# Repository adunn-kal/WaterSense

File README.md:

# WaterSense
 Main firmware for the Water Sense project.
 
 See https://adunn-kal.github.io/WaterSense/ for more details.

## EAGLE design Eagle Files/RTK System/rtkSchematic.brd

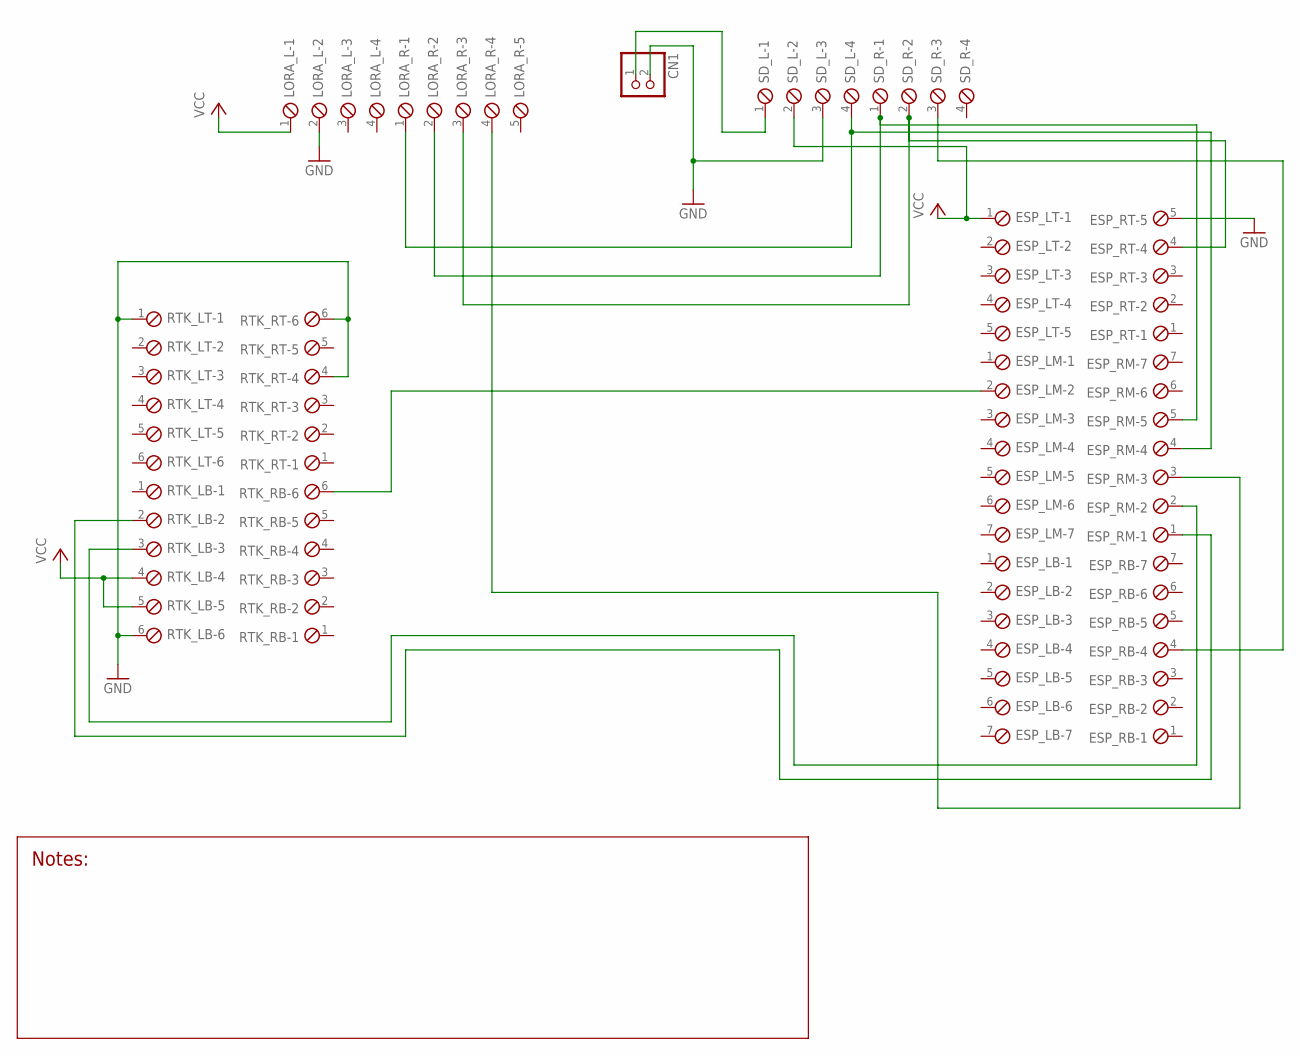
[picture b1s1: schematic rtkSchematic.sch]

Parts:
CN1: JST_2PIN-SMT-RA; JST-PH-2-SMT-RA
ESP_LB: SCREWTERM_7P_254; 7POL254
ESP_LM: SCREWTERM_7P_254; 7POL254
ESP_LT: SCREWTERM_5P_254; 5POL254
ESP_RB: SCREWTERM_7P_254; 7POL254
ESP_RM: SCREWTERM_7P_254; 7POL254
ESP_RT: SCREWTERM_5P_254; 5POL254
LORA_L: SCREWTERM_4P_254; 4POL254
LORA_R: SCREWTERM_5P_254; 5POL254
RTK_LB: SCREWTERM_6P_254; 6POL254
RTK_LT: SCREWTERM_6P_254; 6POL254
RTK_RB: SCREWTERM_6P_254; 6POL254
RTK_RT: SCREWTERM_6P_254; 6POL254
SD_L: SCREWTERM_4P_254; 4POL254
SD_R: SCREWTERM_4P_254; 4POL254

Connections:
GND: CN1.2 (1), ESP_RT.5, LORA_L.2, RTK_LB.6, RTK_LT.1, RTK_RT.4, RTK_RT.6, SD_L.3
unnamed: ESP_LM.2, RTK_RB.6
unnamed: CN1.1 (2), SD_L.1
unnamed: ESP_RM.4, LORA_R.1, SD_L.4
unnamed: ESP_RM.5, LORA_R.2, SD_R.1
unnamed: ESP_RT.4, LORA_R.3, SD_R.2
unnamed: ESP_RB.4, SD_R.3
unnamed: ESP_RM.2, RTK_LB.3
unnamed: ESP_RM.1, RTK_LB.2
unnamed: ESP_RM.3, LORA_R.4
VCC: ESP_LT.1, LORA_L.1, RTK_LB.4, RTK_LB.5, SD_L.2

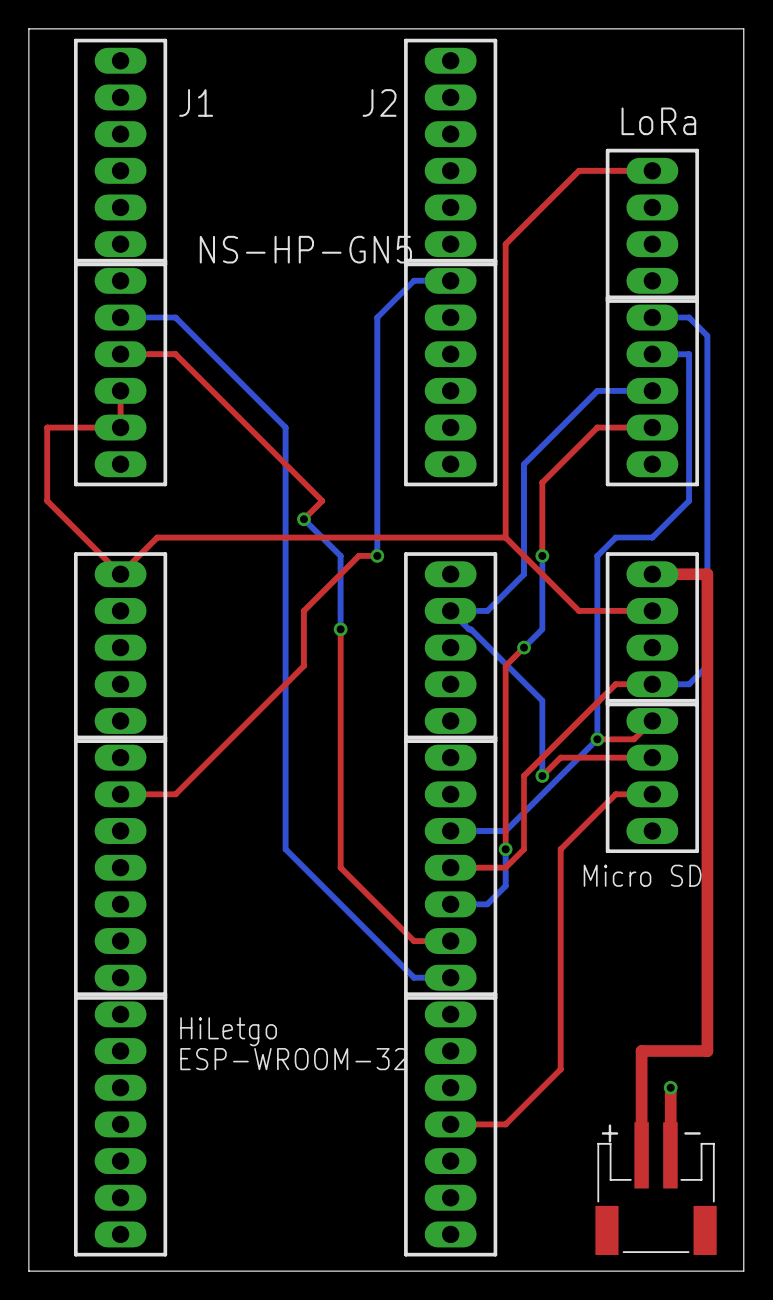
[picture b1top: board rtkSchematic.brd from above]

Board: 2 copper layers, 49.5 x 86.0 mm, 15 parts (0 on the bottom side), 11 nets.

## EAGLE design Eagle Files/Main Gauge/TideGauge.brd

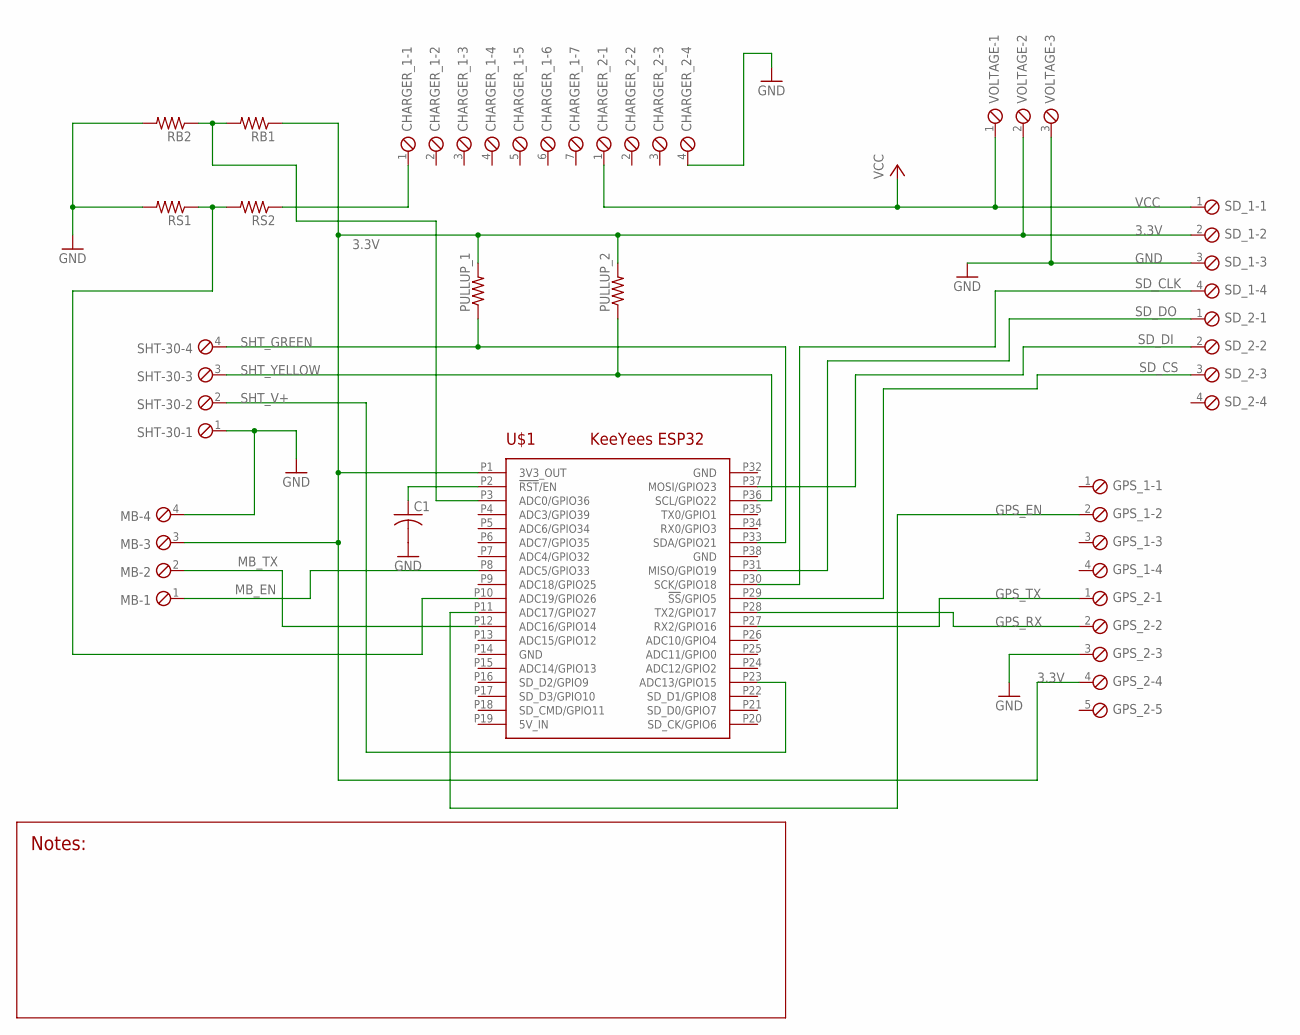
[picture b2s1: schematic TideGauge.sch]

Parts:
C1: C-USC0805; C0805
CHARGER_1: SCREWTERM_7P_254; 7POL254
CHARGER_2: SCREWTERM_4P_254; 4POL254
GPS_1: SCREWTERM_4P_254; 4POL254
GPS_2: SCREWTERM_5P_254; 5POL254
MB: SCREWTERM_4P_254; 4POL254
PULLUP_1, PULLUP_2: R-US_M0805; M0805
RB1, RB2: R-US_R0805; R0805
RS1, RS2: R-US_R0805; R0805
SD_1, SD_2: SCREWTERM_4P_254; 4POL254
SHT-30: SCREWTERM_4P_254; 4POL254
U$1: KEEYEES_ESP32
VOLTAGE: SCREWTERM_3P_254; 3POL254

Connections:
3.3V: GPS_2.4, MB.3, PULLUP_1.2, PULLUP_2.2, RB1.1, SD_1.2, U$1.P1 (3V3_OUT), VOLTAGE.2
5V_IN: U$1.P19 (5V_IN)
GND: C1.2, CHARGER_2.4, GPS_2.3, MB.4, RB2.2, RS1.2, SD_1.3, SHT-30.1, U$1.P14 (GND), U$1.P32 (GND), U$1.P38 (GND), VOLTAGE.3
GPS_EN: GPS_1.2, U$1.P11 (ADC17/GPIO27)
GPS_RX: GPS_2.2, U$1.P28 (TX2/GPIO17)
GPS_TX: GPS_2.1, U$1.P27 (RX2/GPIO16)
MB_EN: MB.1, U$1.P8 (ADC5/GPIO33)
MB_TX: MB.2, U$1.P12 (ADC16/GPIO14)
unnamed: C1.1, U$1.P2 (!RST!/EN)
unnamed: CHARGER_1.1, RS2.1
unnamed: RS1.1, RS2.2, U$1.P10 (ADC19/GPIO26)
unnamed: RB1.2, RB2.1, U$1.P3 (ADC0/GPIO36)
SD_CLK: SD_1.4, U$1.P30 (SCK/GPIO18)
SD_CS: SD_2.3, U$1.P29 (!SS!/GPIO5)
SD_DI: SD_2.2, U$1.P37 (MOSI/GPIO23)
SD_DO: SD_2.1, U$1.P31 (MISO/GPIO19)
SHT_GREEN: PULLUP_1.1, SHT-30.4, U$1.P33 (SDA/GPIO21)
SHT_V+: SHT-30.2, U$1.P23 (ADC13/GPIO15)
SHT_YELLOW: PULLUP_2.1, SHT-30.3, U$1.P36 (SCL/GPIO22)
VCC: CHARGER_2.1, SD_1.1, VOLTAGE.1

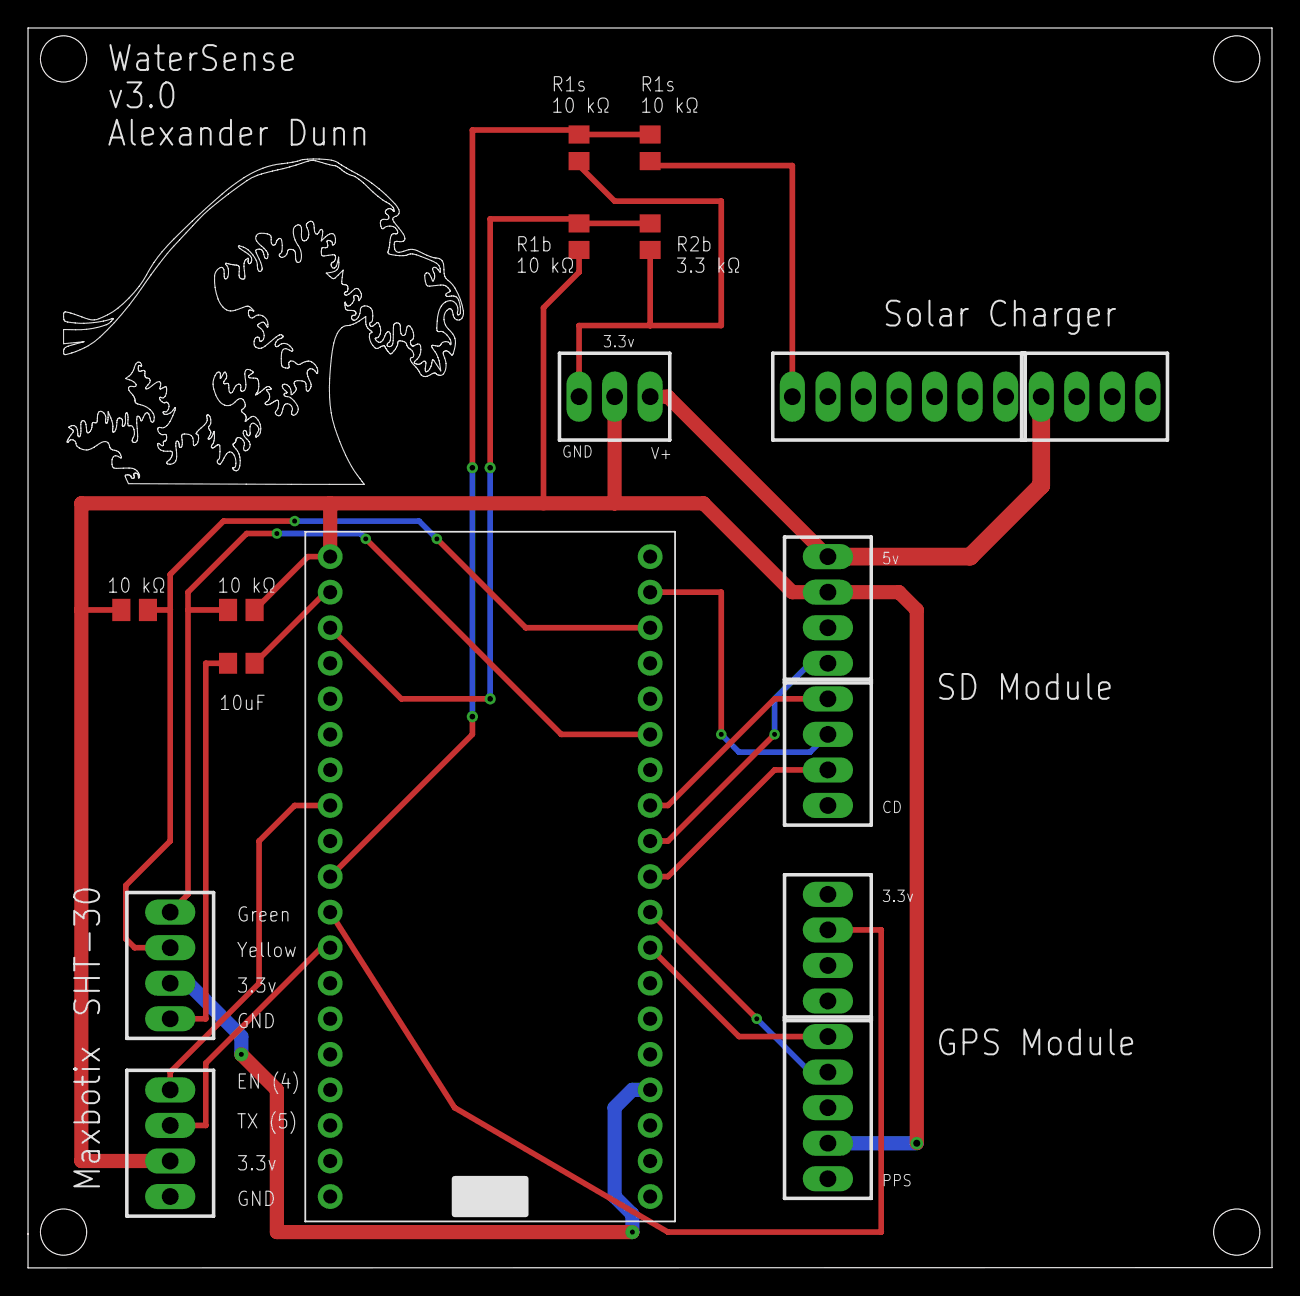
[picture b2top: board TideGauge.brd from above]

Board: 2 copper layers, 88.9 x 88.6 mm, 17 parts (0 on the bottom side), 19 nets.

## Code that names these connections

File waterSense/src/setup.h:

/**
 * @file setup.h
 * @author Alexander Dunn
 * @brief A file to contain all setup information
 * @version 0.1
 * @date 2023-02-05
 * 
 * @copyright Copyright (c) 2023
 * 
 */

//-----------------------------------------------------------------------------------------------------||
//---------- Define Constants -------------------------------------------------------------------------||

/**
 * @brief Define this constant to enable continuous measurements
 * @details Writes data to the SD card at the specified read intervals but does not sleep
 * 
 */
// #define CONTINUOUS

/**
 * @brief Define this constant to enable variable duty cycle
 * @details If undefined, HI_READ and HI_ALLIGN are used
 * 
 */
#define VARIABLE_DUTY ///< Define this constant to enable variable duty cycle
//----------------------||
#define HI_READ 60*5  //||
#define MID_READ 60*2 //||
#define LOW_READ 60*1 //||
//                    //||
#define HI_ALLIGN 10  //||
#define MID_ALLIGN 30 //||
#define LOW_ALLIGN 60 //||
//----------------------||

#define WAKE_CYCLES 15 ///< Number of wake cycles between reset checks
#define FIX_DELAY 60*2 ///< Seconds to wait for first GPS fix
// #define FIX_DELAY 1 ///< Seconds to wait for first GPS fix

#define WATCH_TIMER 15*1000 ///< ms of hang time before triggering a reset

#define MEASUREMENT_PERIOD 100 ///< Measurement task period in ms
#define SD_PERIOD 10 ///< SD task period in ms
#define CLOCK_PERIOD 10 ///< Clock task period in ms
#define SLEEP_PERIOD 100 ///< Sleep task period in ms
#define VOLTAGE_PERIOD 1000 ///< Voltage task period in ms
#define WATCHDOG_PERIOD 100 ///< Watchdog task period in ms

// #define R1b 9.54 ///< Larger resistor for battery voltage divider
// #define R2b 2.96 ///< Smaller resistor for battery voltage divider
#define R1b 9.25 ///< Larger resistor for battery voltage divider
#define R2b 3.3 ///< Smaller resistor for battery voltage divider

#define R1s 10.0 ///< Resistor for solar panel voltage divider
#define R2s 10.0 ///< Resistor for solar panel voltage divider

//-----------------------------------------------------------------------------------------------------||
//-----------------------------------------------------------------------------------------------------||










//-----------------------------------------------------------------------------------------------------||
//---------- Define Pins ------------------------------------------------------------------------------||

#define SD_CS GPIO_NUM_5 ///< SD card chip select pin

#define SONAR_RX GPIO_NUM_14 ///< Sonar sensor receive pin
#define SONAR_TX GPIO_NUM_32 ///< Sonar sensor transmit pin

/**
 * @brief Sonar sensor enable pin
 * @details Sonar measurements are disbale when this pin is pulled low
 * 
 */
#define SONAR_EN GPIO_NUM_33

#define GPS_RX GPIO_NUM_16 ///< GPS receive pin
#define GPS_TX GPIO_NUM_17 ///< GPS transmit pin

/**
 * @brief GPS enable pin
 * @details GPS measurements are disabled when this pin is pulled low
 * 
 */
#define GPS_EN GPIO_NUM_27

#define TEMP_SENSOR_ADDRESS 0x44 ///< Temperature and humidity sensor hex address

/**
 * @brief Temperature/humidity sensor enable pin
 * @details Temperature and humidity measurements are disabled when this pin is pulled low
 * 
 */
#define TEMP_EN GPIO_NUM_15

#define ADC_PIN GPIO_NUM_26

//-----------------------------------------------------------------------------------------------------||
//-----------------------------------------------------------------------------------------------------||

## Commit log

2023-01-02 added main file
2023-01-02 added sdData class
2023-01-02 added maxbotix class
2023-01-02 added gpsClock class
2023-01-02 added adafruit temp hum class
2023-01-02 added ME 507 classes
2023-01-02 added docs
2023-01-02 replaced docs
2023-01-30 Moved .h and .cpp files into source directory. No more hosting needed
2023-02-02 Added solar voltage task
2023-02-02 Added solar voltage tracking and blinking LED
2023-02-02 Removed blinking functionality (didn't work)
2023-02-02 Removed old libdeps
2023-02-03 Added LED support within classes
2023-02-03 Added logFile with location data
2023-02-04 Fixed lat long format
2023-02-04 Added battery and voltage data storage
2023-02-04 Added battery and solar voltage functionality. Variable duty cycle based on battery voltage
2023-02-06 Reorganized into separate files
2023-02-06 Updated docs
2023-02-06 Testing docs
2023-02-06 Updating docs
2023-02-06 Testing to make sure duty cycles work
2023-02-13 Added a watchdog task
2023-02-13 Added in internal RTC use
2023-02-15 Fixed low power mode (previously used unit8_t -> overflow issues)
2023-02-15 Added catch for extended sleep times
2023-03-07 Testing
2023-03-08 Added functionality to fix SD file naming
2023-03-09 Added continuous measurement functionality
2023-03-20 Updated code for Kaden's boxes
2023-03-28 Code for Cayucos deployment
2023-04-07 Code For 20 MHZ test
2023-04-07 San Simeon code
2023-04-09 Possible fix for slow clock SD card loss
2023-05-06 Added atmospheric gauge code
2023-05-06 moved things slightly
2023-05-06 Added RTK files
2023-05-06 Added matlab scripts
2023-05-20 cal poly pier P3H
2023-05-23 Updated to include proper naming convention
2023-06-01 San Simeon Gauge
2023-06-13 Added Eagle files
